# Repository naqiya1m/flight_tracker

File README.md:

# flight_tracker

[main project]
This is a pendant that will connect to the internet via bluetooth from a device, allowing it to grab and display the flight information of any plane within 5km of your location which was taken using GPS. Very similar to the prototype in terms of features and display, but still a work in progress.

Buzzer was taken out because I could not source a part small enough. The routing for the buzzer is still going to be on the pcb design but I will leave it unpopulated when I put it together. 

The schematic, pcb, and gerber files are all included, but it has yet to be built and tested. 

Materials:
- screen --> Waveshare 0.71-inch Round IPS LCD
- microcontroller --> Seeed Studio XIAO ESP32-C3
- battery ---> 402020 3.7V 160mAh LiPo Battery

[prototype]
This is a raspberry pi pico w connected to an LCD screen that detects live flights within 5km, buzzes, and then displays the callsign, altitude, km away, country origin, and an arrow pointing in the flight direction.

Materials used:
- raspberry pi pico w
- 1.54 LCD screen
- breadboard/jumper wires
- piezo buzzer

API used: https://opensky-network.org/api/states/all

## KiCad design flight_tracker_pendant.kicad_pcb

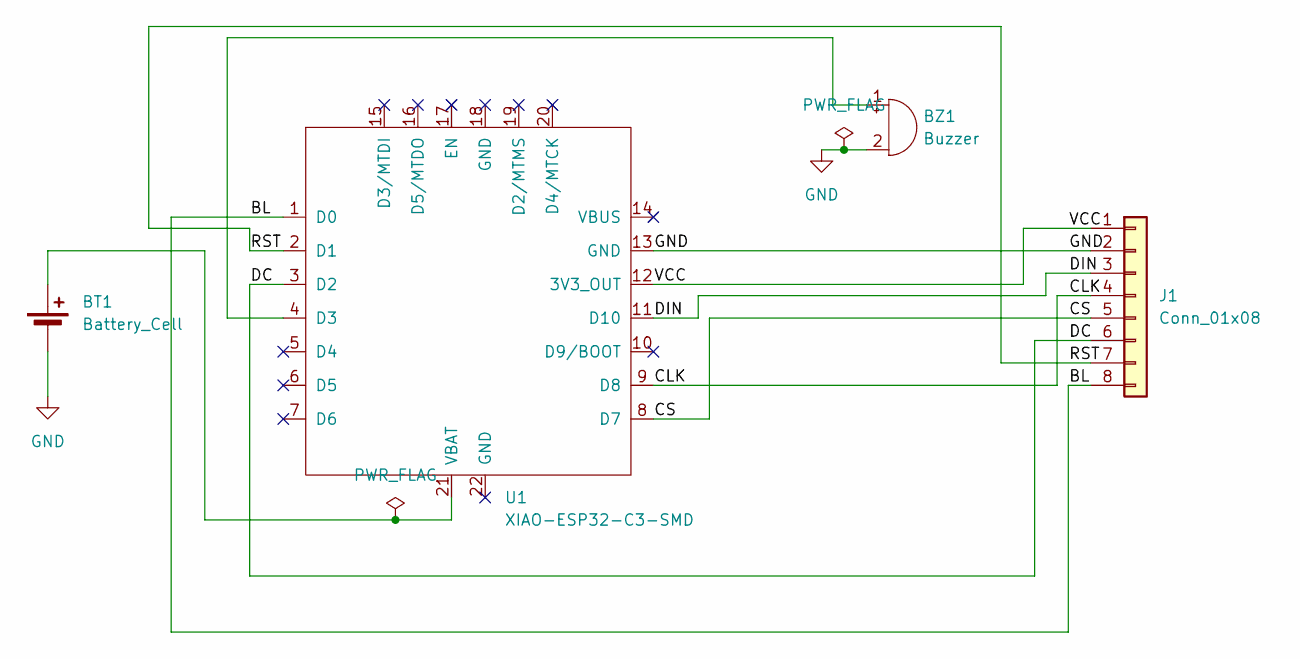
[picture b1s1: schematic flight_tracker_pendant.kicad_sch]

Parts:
BT1: Battery_Cell; PinHeader_1x02_P2.54mm_Vertical
BZ1: Buzzer; CPT-0303-SMT
J1: Conn_01x08; PinHeader_1x08_P2.54mm_Vertical
U1: XIAO-ESP32-C3-SMD; MCU_Seeed_ESP32C3

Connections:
/BL: J1.8, U1.1 (D0)
/CLK: J1.4, U1.9 (D8)
/CS: J1.5, U1.8 (D7)
/DC: J1.6, U1.3 (D2)
/DIN: J1.3, U1.11 (D10)
/RST: J1.7, U1.2 (D1)
/VCC: J1.1, U1.12 (3V3_OUT)
GND: BT1.2 (-), BZ1.2 (-), J1.2, U1.13 (GND)
unnamed: BT1.1 (+), U1.21 (VBAT)
unnamed: BZ1.1 (+), U1.4 (D3)

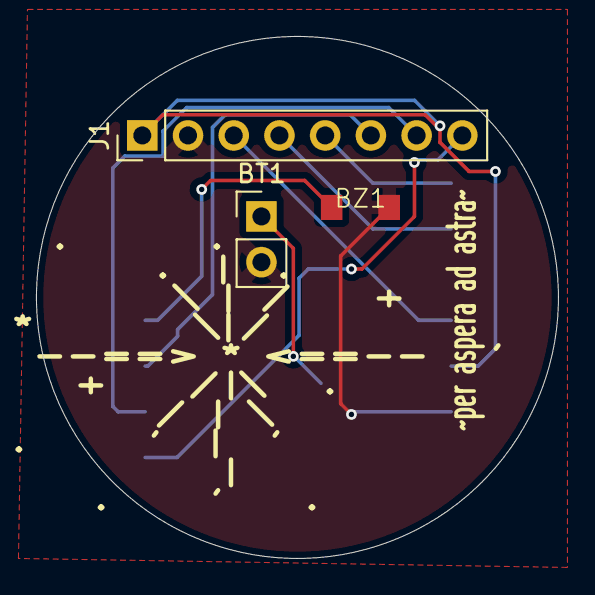
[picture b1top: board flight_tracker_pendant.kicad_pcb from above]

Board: 2 copper layers, 29.0 x 29.0 mm, 4 parts (1 on the bottom side), 10 nets.
